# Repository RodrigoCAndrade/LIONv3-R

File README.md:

<div align="center">
  
</div>

<h1 align="center">LIONv3-R Module</h1>

<p align="center">

</p>

<br>

## Overview

The LIONv3-R is an IoT and Direct-to-Satellite (DtS) board built around the ESP32-C6, with 16 MB of external flash and local connectivity over Wi-Fi, Zigbee and Thread. Its radio supports LR-FHSS alongside conventional LoRa, enabling reliable uplinks to satellites or terrestrial gateways from remote sites, at device densities conventional LoRa cannot sustain. By bridging local wireless networks with satellite reach, the LIONv3-R is a complete, scalable hardware platform for telemetry, global asset tracking and remote sensing.

## Repository Organization

* `docs`: Systems engineering, datasheets, requirements (SRD), and interface control (ICD).
* `hardware`: Native KiCad project, schematics, and manufacturing files.
* `mechanics`: 3D models, technical drawings, and physical integration constraints.
* `software`: Embedded firmware and support testing scripts.

## Releases

<table>
  <thead>
    <tr>
      <th>Render</th>
      <th>Hardware Revision</th>
      <th>Status</th>
      <th>Latest Release</th>
      <th>Date</th>
      <th>Datasheet</th>
      <th>BOM</th>
      <th>Manufacturing Info</th>
    </tr>
  </thead>
  <tbody>
    <tr>
      <td></td>
      <td>LIONv3-R</td>
      <td>🚧 Development</td>
      <td><a href="#">-</a></td>
      <td>18-08-2026</td>
      <td><a href="#">PDF</a></td>
      <td>-</td>
      <td><a href="#">Gerber</a></td>
    </tr>
  </tbody>
</table>

## Contributing

We welcome contributions to this project! To ensure a smooth collaboration and maintain our engineering standards, please review our [Contribution Guidelines](CONTRIBUTING.md) before opening any issues, modifying the hardware design, or submitting pull requests.

## References

This board was developed from scratch, but draws on the earlier LIONv1 and LIONv2 designed by [Diego Anestor Coutinho](https://github.com/DIEGOVZK) and [Arielli Ajudarte](https://github.com/ari-aju). The v3 introduces several improvements:

- Dedicated low-power MCU on board
- LR-FHSS support and a more capable LoRa transceiver, covering both sub-GHz and S-band
- External flash for store-and-forward applications
- More efficient antenna
- More compact form factor

## License

This project utilizes a dual-licensing approach to maximize flexibility and adoption:

* **Hardware:** The hardware designs and schematics are licensed under the permissive **[CERN-OHL-P-2.0](hardware/LICENSE)** open-hardware license. You are entirely free to use, modify, distribute, and commercialize the design without any copyleft obligations to share your derived works under the same terms.
* **Software:** All embedded firmware and utility scripts are licensed under the **[MIT License](software/LICENSE)**. You are free to use, modify, and distribute the code without restriction, provided the original copyright notice and permission notice are included.

## Acknowledgments

This work was carried out at the National Institute of Telecommunications (Inatel) with the support of three research laboratories. The EMBRAPII Inatel Competence Center for 5G and 6G Networks [(xGMobile)](https://inatel.br/xgmobile/) supported this project through its Talent Development Program (PFT xGMobile), alongside the Radio & Communication Laboratory [(RadioCom Lab)](https://inatel.br/radiocomlab/) and the Wireless and Artificial Intelligence Laboratory [(WAI Lab)](https://inatel.br/wailab/). Many thanks to the researchers and staff of all three laboratories for their help and for the infrastructure that made the LIONv3-R possible.

<p align="center">
  <sub>Built with ❤️ by <a href="https://rodrigoandrade.com">Rodrigo de Carvalho Andrade</a></sub>
</p>

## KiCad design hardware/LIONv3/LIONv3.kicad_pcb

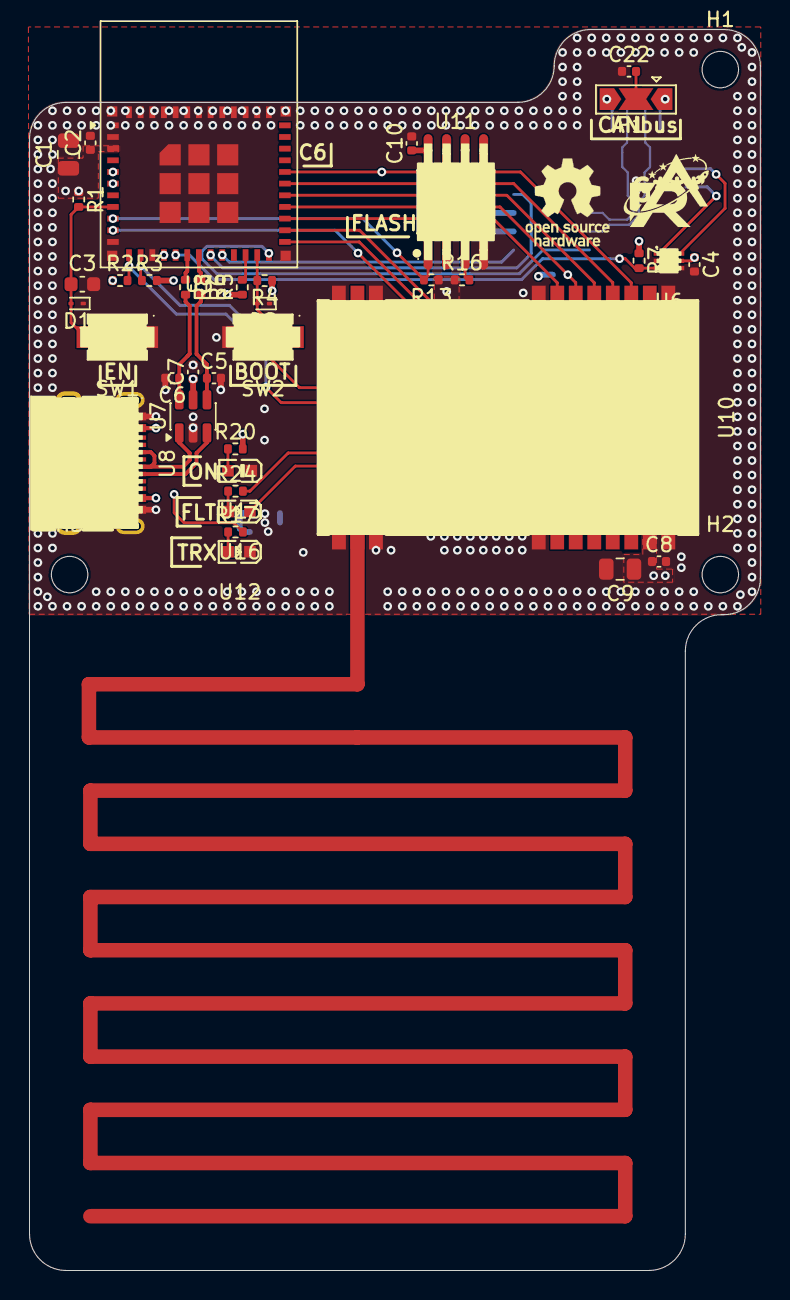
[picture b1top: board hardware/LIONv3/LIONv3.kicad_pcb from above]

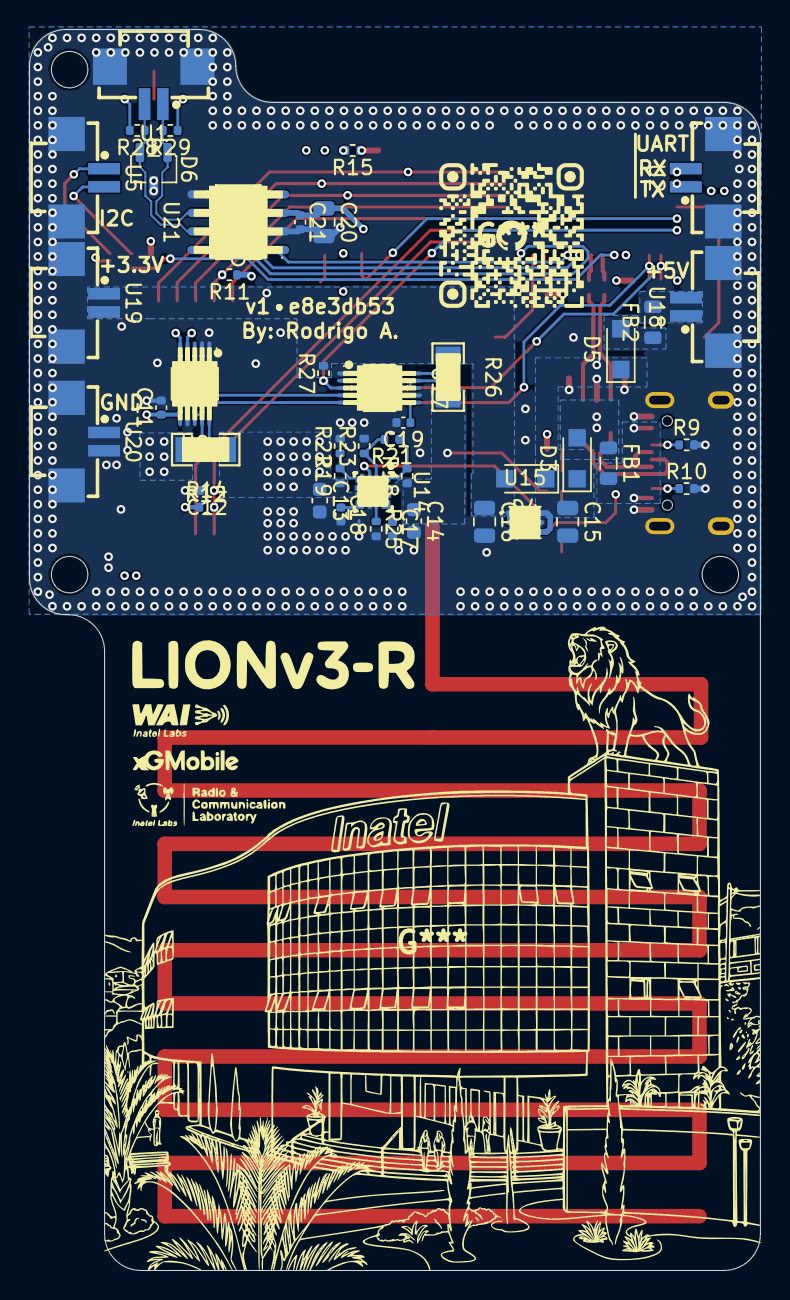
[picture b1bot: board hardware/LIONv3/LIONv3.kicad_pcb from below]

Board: 4 copper layers, 50.1 x 85.2 mm, 85 parts (44 on the bottom side), 56 nets.

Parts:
C1, C9, C15, C16: 22uF; C_0805_2012Metric
C2, C4, C7, C8, C10, C11, C12, C19, C21: 100nF; C_0402_1005Metric
C3, C13, C14: 1uF; C_0603_1608Metric
C5, C6: DNP; C_0402_1005Metric
C17: 3.3nF; C_0402_1005Metric
C18: 2.2nF; C_0402_1005Metric
C20: 10uF; C_0805_2012Metric
C22: 4.7nF; C_0402_1005Metric
D1, D2: ESD9B3.3ST5G; D_SOD-923
D3, D4, D5: PMEG2010ER; Nexperia_CFP3_SOD-123W
D6: TI ESD752DBZR; SOT-23-3
FB1, FB2: BLM21PG221SN1D; L_0805_2012Metric
H1, H2, H3: MountingHole_Pad; MountingHole_2.5mm
JP1: SolderJumper_3_Open; SolderJumper-3_P2.0mm_Open_TrianglePad1.0x1.5mm
R1, R4, R5, R11, R13, R14, R15, R16, R21, R22, R27: 10k; R_0402_1005Metric
R2, R3, R7: 4.7k; R_0402_1005Metric
R6, R8: 0; R_0402_1005Metric
R9, R10: 5.1k; R_0402_1005Metric
R12, R26: 50m; R1206
R17, R20: 120; R_0402_1005Metric
R18: 60.4k; R_0402_1005Metric
R19: 15k; R_0402_1005Metric
R23: 34.8k; R_0402_1005Metric
R24: 430; R_0402_1005Metric
R25: 3.32k; R_0402_1005Metric
R28, R29: 59; R_0402_1005Metric
SW1: RESET; KEY-SMD_L3.9-W3.0-LS5.0
SW2: BOOT; KEY-SMD_L3.9-W3.0-LS5.0
U1, U2, U5, U18, U19, U20: HC-1_25-2PWT; CONN-SMD_2P-P1.25-HC-1.25-2PWT
U3: ESP32-C6-MINI-1-N4; ESP32-C6-MINI-1
U6: TMP112AIDRLR; SOT-563_L1.6-W1.2-P0.50-LS1.6-BR
U7: USBLC6-2SC6; SOT-23-6
U8: TYPE-C_16PIN_2MD(073); USB-C-SMD_TYPE-C-16PIN-2MD-073
U9, U17: INA226AIDGSR; MSOP-10_L3.0-W3.0-P0.50-LS5.0-BL
U10: E80-900M2213S; WIFIM-SMD_22P-L26.0-W16.0-P1.27-TL
U11: W25Q16JVSSIQTR; SOIC-8_L5.3-W5.3-P1.27-LS8.0-BL
U12: XL-1608UBC-04; LED0603-RD_BLUE
U13: XL-1608UGC-04; LED0603-RD_GREEN
U14: TPS259474ARPWR; VQFN-10_L2.0-W2.0-P0.45-TL
U15: TLV76733DRVR; WSON-6_L2.0-W2.0-P0.65-TL-EP
U16: XL-1608SURC-06; LED0603-RD_RED
U21: TCAN3414DR; SOIC-8_L4.9-W3.9-P1.27-LS6.0-BL

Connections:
3.3V_RF: C8.1, C9.1, R12.2, R14.1, U9.8 (VBUS), U9.9 (VIN-), U10.25 (VCC)
+3.3V: C1.1, C2.1, C4.1, C10.1, C11.1, C13.1, C20.1, C21.1, R1.1, R2.1, R3.2, R4.1, R5.1, R7.1, R11.1, R12.1, R13.1, R15.1, R16.1, R19.1, R20.2, U3.3 (3V3), U6.5 (V+), U9.6 (VS+), U9.10 (VIN+), U11.8 (VCC), U14.6 (OUT), U21.3 (VCC)
+3.3V_LDO: C16.1, C19.1, D4.2 (A), R26.1, R27.2, U15.1 (OUT), U15.2 (FB/SNS), U17.6 (VS+), U17.10 (VIN+), U19.1, U19.2
+3.3V_eFuse: C14.1, R18.1, R24.2, R26.2, U14.5 (IN), U17.8 (VBUS), U17.9 (VIN-)
+4.69V: C7.1, C15.1, D3.1 (K), D4.1 (K), D5.1 (K), U7.5 (VBUS), U15.4 (EN), U15.6 (IN)
/CAN_N: D6.1 (K), R29.2, U1.1, U21.6 (CANL)
/CAN_P: D6.2 (K), R28.1, U1.2, U21.7 (CANH)
/CAN_RX: U3.19 (IO14), U21.4 (RXD)
/CAN_STB: U3.24 (IO18), U21.8 (STB)
/CAN_TX: U3.20 (IO15), U21.1 (TXD)
/D+: U7.3 (I/O2), U8.A6 (Dp1), U8.B6 (Dp2)
/D-: U7.1 (I/O1), U8.A7 (Dn1), U8.B7 (Dn2)
/ESP_USB_D+: R6.1, U3.18 (IO13)
/ESP_USB_D-: R8.1, U3.17 (IO12)
/FLASH_CS#: R13.2, U3.9 (IO4), U11.1 (CS#)
/I2C_SCL: R3.1, U3.13 (IO1), U5.2, U6.1 (SCL), U9.5 (SCL), U17.5 (SCL)
/I2C_SDA: R2.2, U3.12 (IO0), U5.1, U6.6 (SDA), U9.4 (SDA), U17.2 (A0), U17.4 (SDA)
/INA_ALERT: R27.1, U3.10 (IO5), U17.3 (Alert)
/IO8: R5.2, U3.22 (IO8)
/IO9: D2.2 (A2), R4.2, SW2.1, U3.23 (IO9)
/LR_BUSY: U3.27 (IO21), U10.7 (BUSY)
/LR_CS#: R11.2, U3.28 (IO22), U10.6 (CS#)
/LR_IRQ: U3.26 (IO20), U10.22 (DIO9)
/LR_LED: R17.2, U3.15 (IO6)
/LR_RST: C12.1, R14.2, U3.25 (IO19), U10.21 (LR_NRESET)
/POWER/LED_FAULT: U14.3 (PG/AUXOFF), U16.1 (K)
/SPI_PICO: U3.30 (RXD0), U10.4 (PICO), U11.5 (DI/IO0)
/SPI_POCI: U3.31 (TXD0), U10.3 (POCI), U11.2 (DO/IO1)
/SPI_SCK: U3.29 (IO23), U10.5 (SCK), U11.6 (CLK)
/TMP_ALERT: R7.2, U3.16 (IO7), U6.3 (ALERT)
/UART_RX: U2.2, U3.5 (IO2)
/UART_TX: U2.1, U3.6 (IO3)
/USB_D+: C5.1, R6.2, U7.4 (I/O2)
/USB_D-: C6.1, R8.2, U7.6 (I/O1)
GND: C1.2, C2.2, C3.2, C4.2, C5.2, C6.2, C7.2, C8.2, C9.2, C10.2, C11.2, C12.2, C13.2, C14.2, C15.2, C16.2, C17.2, C18.2, C19.2, C20.2, C21.2, C22.1, D1.1 (A1), D2.1 (A1), D6.3 (A), R9.2, R10.2, R22.2, R23.2, R25.2, SW1.1, SW2.2, U1.3, U1.4, U2.3, U2.4, U3.1 (GND), U3.2 (GND), U3.11 (GND), U3.14 (GND), U3.36 (GND), U3.37 (GND), U3.38 (GND), U3.39 (GND), U3.40 (GND), U3.41 (GND), U3.42 (GND), U3.43 (GND), U3.44 (GND), U3.45 (GND), U3.46 (GND), U3.47 (GND), U3.48 (GND), U3.49 (GND), U3.50 (GND), U3.51 (GND), U3.52 (GND), U3.53 (GND), U5.3, U5.4, U6.2 (GND), U6.4 (ADD0), U7.2 (GND), U8.13 (EH), U8.14 (EH), U8.A1B12 (GND), U8.B1A12 (GND), U9.1 (A1), U9.2 (A0), U9.7 (GND), U10.1 (GND), U10.8 (GND), U10.11 (GND), U10.13 (GND), U10.14 (GND), U10.16 (GND), U10.19 (GND), U10.26 (GND), U11.4 (GND), U12.1 (K), U13.1 (K), U14.8 (GND), U15.3 (GND), U15.5 (GND), U15.7 (EP), U17.1 (A1), U17.7 (GND), U18.3, U18.4, U19.3, U19.4, U20.1, U20.2, U20.3, U20.4, U21.2 (GND), U21.5 (SHDN/VIO)
unnamed: C3.1, D1.2 (A2), R1.2, SW1.2, U3.8 (EN)
unnamed: D3.2 (A), FB1.1
unnamed: D5.2 (A), FB2.1
unnamed: FB1.2, U8.A4B9 (VBUS), U8.B4A9 (VBUS)
unnamed: FB2.2, U18.1, U18.2
unnamed: JP1.1 (A), R28.2
unnamed: JP1.3 (B), R29.1
unnamed: C22.2, JP1.2 (C)
unnamed: R9.1, U8.A5 (CC1)
unnamed: R10.1, U8.B5 (CC2)
unnamed: R16.2, U11.3 (IO2)
unnamed: R15.2, U11.7 (IO3)
unnamed: R17.1, U12.2 (A)
unnamed: R20.1, U13.2 (A)
unnamed: C18.1, U14.7 (DVDT)
unnamed: R18.2, R21.1, U14.1 (EN/UVLO)
unnamed: R19.2, R22.1, U14.4 (FLT#/PGTH)
unnamed: R25.1, U14.9 (ILM)
unnamed: C17.1, U14.10 (ITIMER)
unnamed: R21.2, R23.1, U14.2 (OVLO/OVCSEL)
unnamed: R24.1, U16.2 (A)

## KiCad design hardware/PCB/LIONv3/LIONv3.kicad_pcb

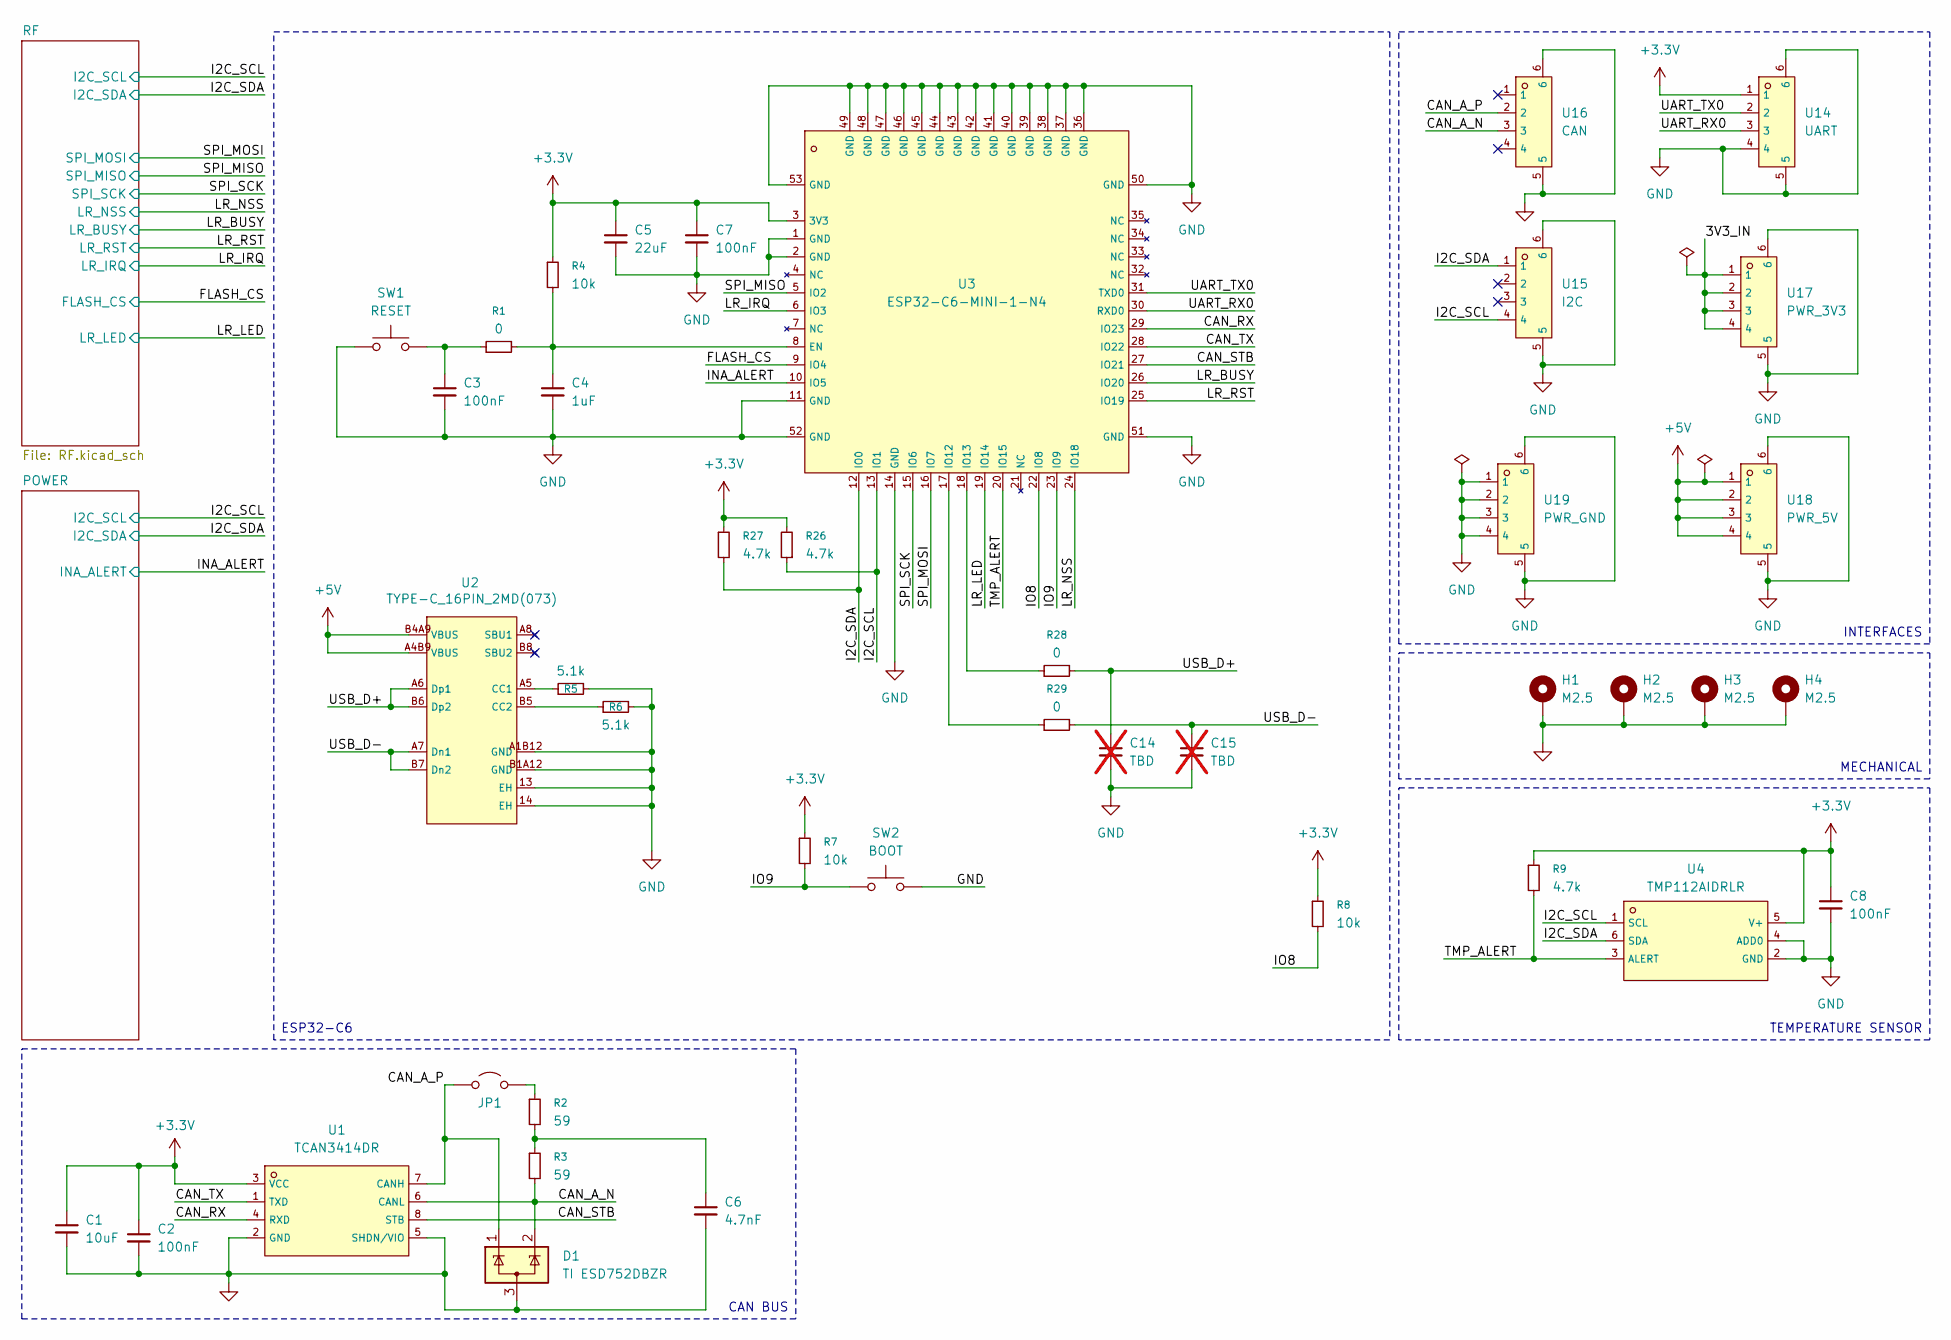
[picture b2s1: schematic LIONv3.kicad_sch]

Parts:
C1: 10uF; C_0805_2012Metric; LCSC C440198
C2, C3, C7, C8: 100nF; C_0402_1005Metric; LCSC C307331
C4: 1uF; C_0603_1608Metric; LCSC C15849
C5: 22uF; C_0805_2012Metric; LCSC C45783
C6: 4.7nF; C_0402_1005Metric; LCSC C1538
C14, C15: TBD; C_0402_1005Metric; not fitted
D1: TI ESD752DBZR; SOT-23-3; LCSC C20345397
H1, H2, H3, H4: M2.5; MountingHole_2.5mm_Pad_Via
JP1: Jumper_2_Open; SolderJumper-2_P1.3mm_Open_TrianglePad1.0x1.5mm
R1, R28, R29: 0; R_0402_1005Metric; LCSC C17168
R2, R3: 59; R_0402_1005Metric; LCSC C2998103
R4, R7, R8: 10k; R_0402_1005Metric; LCSC C25744
R5, R6: 5.1k; R_0402_1005Metric; LCSC C25905
R9, R26, R27: 4.7k; R_0402_1005Metric; LCSC C25900
SW1: RESET; KEY-SMD_L3.9-W3.0-LS5.0; LCSC C5373431
SW2: BOOT; KEY-SMD_L3.9-W3.0-LS5.0; LCSC C5373431
U1: TCAN3414DR; SOIC-8_L4.9-W3.9-P1.27-LS6.0-BL; LCSC C22396693
U2: TYPE-C_16PIN_2MD(073); USB-C-SMD_TYPE-C-16PIN-2MD-073; LCSC C2765186
U3: ESP32-C6-MINI-1-N4; WIFIM-SMD_61P-L16.6-W13.2-P0.80-ESP32-C6-MINI-1-N4; LCSC C5736265
U4: TMP112AIDRLR; SOT-563_L1.6-W1.2-P0.50-LS1.6-BR; LCSC C28927
U14: UART; CONN-SMD_4P-P1.25_53261-0471; LCSC C696092
U15: I2C; CONN-SMD_4P-P1.25_53261-0471; LCSC C696092
U16: CAN; CONN-SMD_4P-P1.25_53261-0471; LCSC C696092
U17: PWR_3V3; CONN-SMD_4P-P1.25_53261-0471; LCSC C696092
U18: PWR_5V; CONN-SMD_4P-P1.25_53261-0471; LCSC C696092
U19: PWR_GND; CONN-SMD_4P-P1.25_53261-0471; LCSC C696092

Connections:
+3.3V: C1.1, C2.1, C5.1, C7.1, C8.1, R4.1, R7.1, R8.1, R9.1, R26.2, R27.1, U1.3 (VCC), U3.3 (3V3), U4.5 (V+), U14.1; also elsewhere on the board
+5V: U2.A4B9 (VBUS), U2.B4A9 (VBUS), U18.1, U18.2, U18.3, U18.4; also elsewhere on the board
/3V3_IN: U17.1, U17.2, U17.3, U17.4
/CAN_A_N: D1.2 (K), R3.2, U1.6 (CANL), U16.3
/CAN_A_P: D1.1 (K), JP1.1 (A), U1.7 (CANH), U16.2
/CAN_RX: U1.4 (RXD), U3.29 (IO23)
/CAN_STB: U1.8 (STB), U3.27 (IO21)
/CAN_TX: U1.1 (TXD), U3.28 (IO22)
/FLASH_CS: U3.9 (IO4); also elsewhere on the board
/I2C_SCL: R26.1, U3.13 (IO1), U4.1 (SCL), U15.4; also elsewhere on the board
/I2C_SDA: R27.2, U3.12 (IO0), U4.6 (SDA), U15.1; also elsewhere on the board
/INA_ALERT: U3.10 (IO5); also elsewhere on the board
/IO8: R8.2, U3.22 (IO8)
/IO9: R7.2, SW2.1, U3.23 (IO9)
/LR_BUSY: U3.26 (IO20); also elsewhere on the board
/LR_IRQ: U3.6 (IO3); also elsewhere on the board
/LR_LED: U3.19 (IO14); also elsewhere on the board
/LR_NSS: U3.24 (IO18); also elsewhere on the board
/LR_RST: U3.25 (IO19); also elsewhere on the board
/SPI_MISO: U3.5 (IO2); also elsewhere on the board
/SPI_MOSI: U3.16 (IO7); also elsewhere on the board
/SPI_SCK: U3.15 (IO6); also elsewhere on the board
/TMP_ALERT: R9.2, U3.20 (IO15), U4.3 (ALERT)
/UART_RX0: U3.30 (RXD0), U14.3
/UART_TX0: U3.31 (TXD0), U14.2
/USB_D+: C14.1, R28.2, U2.A6 (Dp1), U2.B6 (Dp2)
/USB_D-: C15.1, R29.2, U2.A7 (Dn1), U2.B7 (Dn2)
GND: C1.2, C2.2, C3.2, C4.2, C5.2, C6.2, C7.2, C8.2, C14.2, C15.2, D1.3 (A), H1.1, H2.1, H3.1, H4.1, R5.2, R6.2, SW1.1, SW2.2, U1.2 (GND), U1.5 (SHDN/VIO), U2.13 (EH), U2.14 (EH), U2.A1B12 (GND), U2.B1A12 (GND), U3.1 (GND), U3.2 (GND), U3.11 (GND), U3.14 (GND), U3.36 (GND), U3.37 (GND), U3.38 (GND), U3.39 (GND), U3.40 (GND), U3.41 (GND), U3.42 (GND), U3.43 (GND), U3.44 (GND), U3.45 (GND), U3.46 (GND), U3.47 (GND), U3.48 (GND), U3.49 (GND), U3.50 (GND), U3.51 (GND), U3.52 (GND), U3.53 (GND), U4.2 (GND), U4.4 (ADD0), U14.4, U14.5, U14.6, U15.5, U15.6, U16.5, U16.6, U17.5, U17.6, U18.5, U18.6, U19.1, U19.2, U19.3, U19.4, U19.5, U19.6; also elsewhere on the board
unnamed: C3.1, R1.1, SW1.2
unnamed: C6.1, R2.2, R3.1
unnamed: JP1.2 (B), R2.1
unnamed: R5.1, U2.A5 (CC1)
unnamed: R6.1, U2.B5 (CC2)
unnamed: C4.1, R1.2, R4.2, U3.8 (EN)
unnamed: R29.1, U3.17 (IO12)
unnamed: R28.1, U3.18 (IO13)

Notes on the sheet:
MECHANICAL
CAN BUS
TEMPERATURE SENSOR
INTERFACES
ESP32-C6

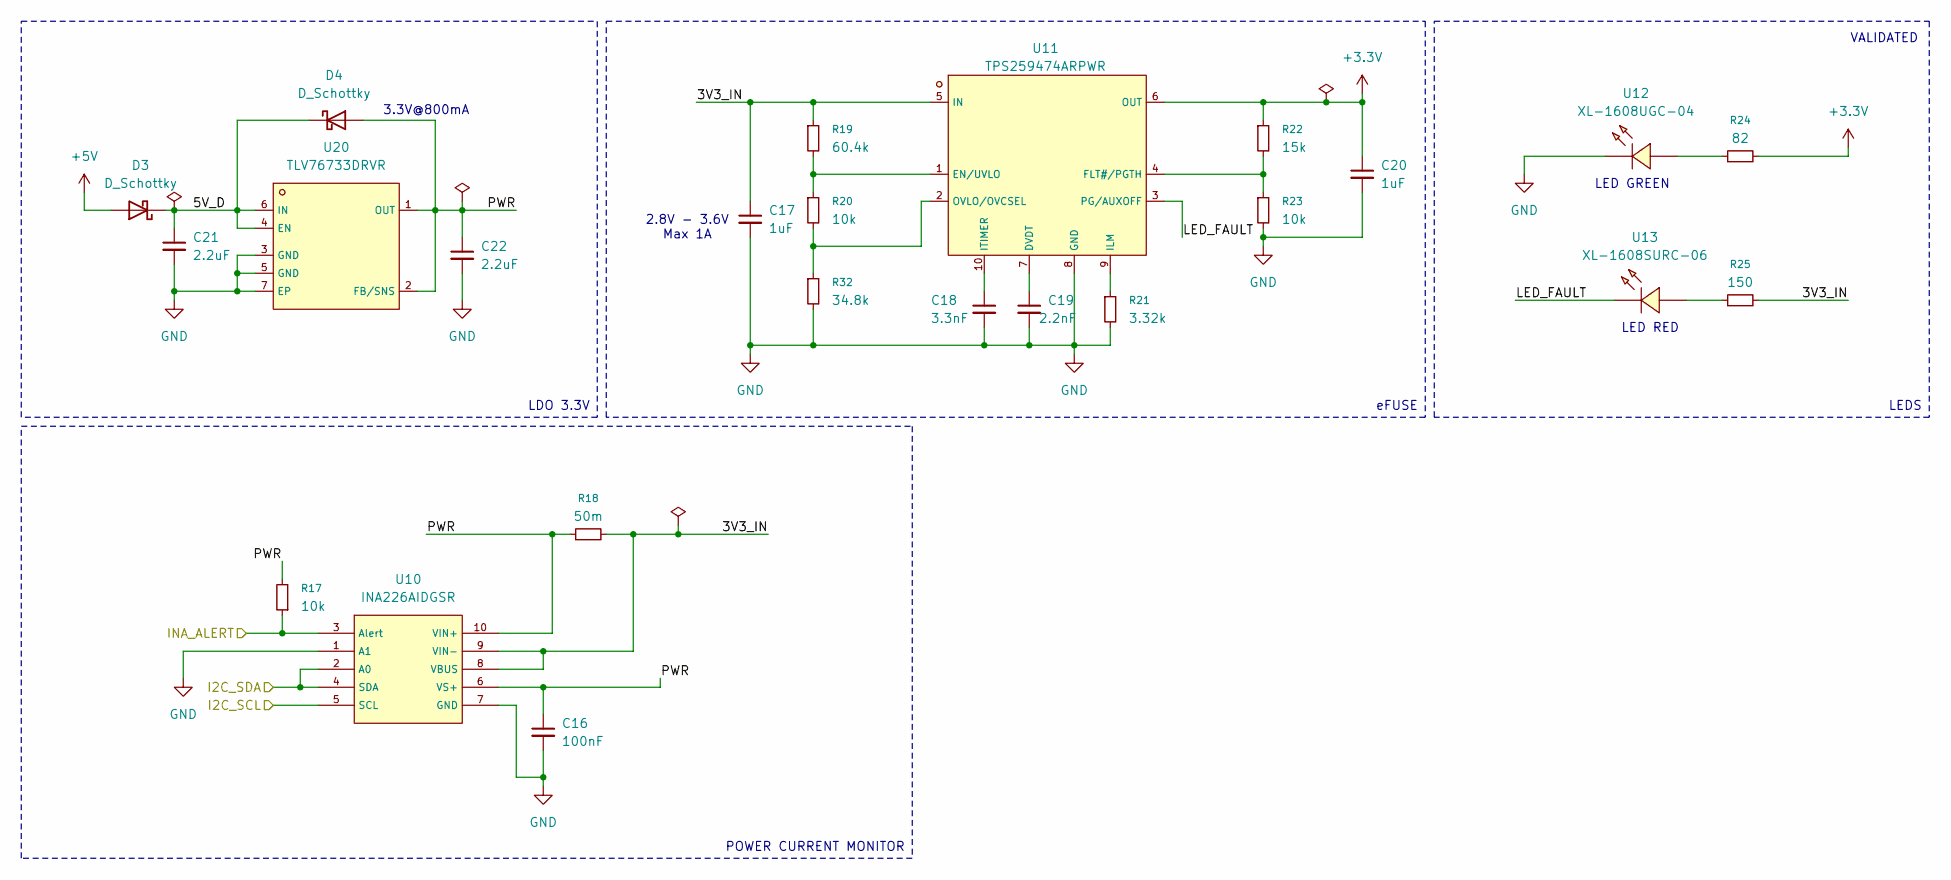
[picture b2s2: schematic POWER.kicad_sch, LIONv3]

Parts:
C16: 100nF; C_0402_1005Metric; LCSC C307331
C17, C20: 1uF; C_0402_1005Metric; LCSC C15849
C18: 3.3nF; C_0402_1005Metric; LCSC C3881585
C19: 2.2nF; C_0402_1005Metric; LCSC C2987940
C21, C22: 2.2uF; C_0603_1608Metric; LCSC C913904
D3, D4: D_Schottky; X2-DFN1006-2_L1.0-W0.6-P0.65-RD; LCSC C2837790
R17, R20, R23: 10k; R_0402_1005Metric; LCSC C25744
R18: 50m; R1206; LCSC C20608719
R19: 60.4k; R_0402_1005Metric; LCSC C2998058
R21: 3.32k; R_0402_1005Metric; LCSC C2998161
R22: 15k; R_0402_1005Metric; LCSC C25756
R24: 82; R_0402_1005Metric; LCSC C2909389
R25: 150; R_0402_1005Metric; LCSC C2909321
R32: 34.8k; R_0402_1005Metric; LCSC C2076772
U10: INA226AIDGSR; MSOP-10_L3.0-W3.0-P0.50-LS5.0-BL; LCSC C49851
U11: TPS259474ARPWR; VQFN-10_L2.0-W2.0-P0.45-TL; LCSC C3662807
U12: XL-1608UGC-04; LED0603-RD_GREEN; LCSC C965804
U13: XL-1608SURC-06; LED0603-RD_RED; LCSC C965799
U20: TLV76733DRVR; WSON-6_L2.0-W2.0-P0.65-TL-EP; LCSC C2848334

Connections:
+3.3V: C20.1, R22.1, R24.2, U11.6 (OUT); also elsewhere on the board
+5V: D3.2 (A); also elsewhere on the board
/I2C_SCL: U10.5 (SCL); also elsewhere on the board
/I2C_SDA: U10.2 (A0), U10.4 (SDA); also elsewhere on the board
/INA_ALERT: R17.1, U10.3 (Alert); also elsewhere on the board
/POWER/3V3_IN: C17.1, R18.2, R19.1, R25.2, U10.8 (VBUS), U10.9 (VIN-), U11.5 (IN)
/POWER/5V_D: C21.1, D3.1 (K), D4.1 (K), U20.4 (EN), U20.6 (IN)
/POWER/LED_FAULT: U11.3 (PG/AUXOFF), U13.1 (K)
/POWER/PWR: C16.1, C22.1, D4.2 (A), R17.2, R18.1, U10.6 (VS+), U10.10 (VIN+), U20.1 (OUT), U20.2 (FB/SNS)
GND: C16.2, C17.2, C18.2, C19.2, C20.2, C21.2, C22.2, R21.2, R23.2, R32.2, U10.1 (A1), U10.7 (GND), U11.8 (GND), U12.1 (K), U20.3 (GND), U20.5 (GND), U20.7 (EP); also elsewhere on the board
unnamed: C19.1, U11.7 (DVDT)
unnamed: R19.2, R20.1, U11.1 (EN/UVLO)
unnamed: R22.2, R23.1, U11.4 (FLT#/PGTH)
unnamed: R21.1, U11.9 (ILM)
unnamed: C18.1, U11.10 (ITIMER)
unnamed: R20.2, R32.1, U11.2 (OVLO/OVCSEL)
unnamed: R24.1, U12.2 (A)
unnamed: R25.1, U13.2 (A)

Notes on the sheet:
3.3V@800mA
2.8V - 3.6V Max 1A
VALIDATED
LED GREEN
LED RED
POWER CURRENT MONITOR
LEDS
LDO 3.3V
eFUSE

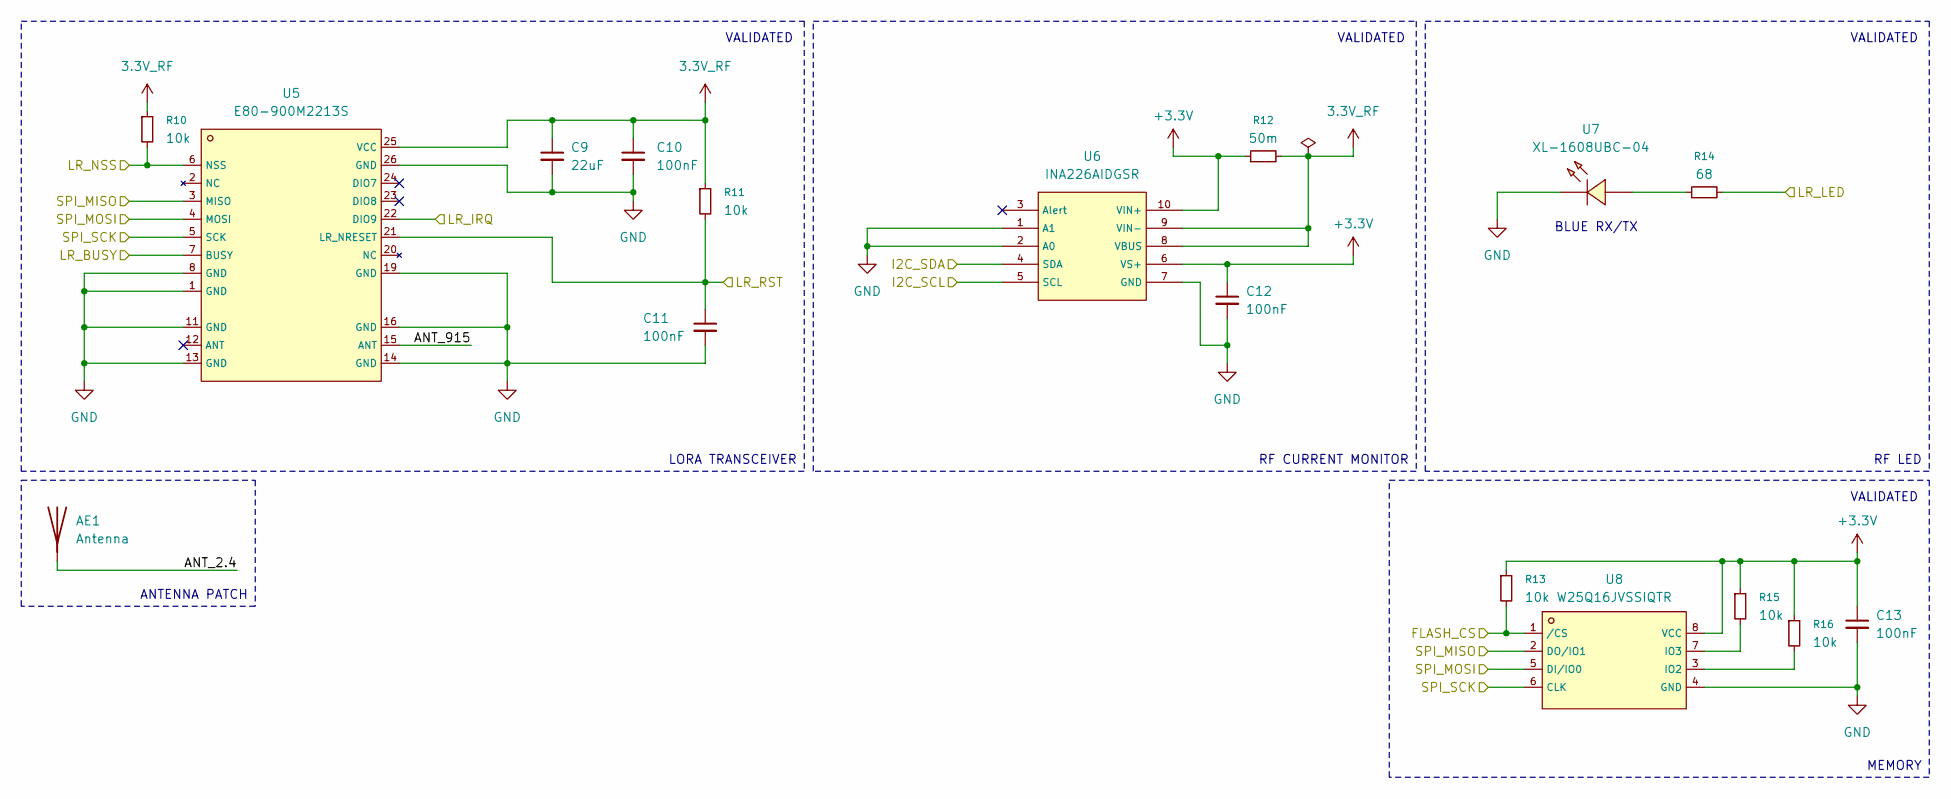
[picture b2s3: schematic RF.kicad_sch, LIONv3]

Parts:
AE1: Antenna
C9: 22uF; C_0805_2012Metric; LCSC C45783
C10, C11, C12, C13: 100nF; C_0402_1005Metric; LCSC C307331
R10, R11, R13, R15, R16: 10k; R_0402_1005Metric; LCSC C25744
R12: 50m; R1206; LCSC C20608719
R14: 68; R_0402_1005Metric; LCSC C2909380
U5: E80-900M2213S; WIFIM-SMD_22P-L26.0-W16.0-P1.27-TL; LCSC C42464134
U6: INA226AIDGSR; MSOP-10_L3.0-W3.0-P0.50-LS5.0-BL; LCSC C49851
U7: XL-1608UBC-04; LED0603-RD_BLUE; LCSC C965807
U8: W25Q16JVSSIQTR; SOIC-8_L5.3-W5.3-P1.27-LS8.0-BL; LCSC C131025

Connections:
3.3V_RF: C9.1, C10.1, R10.1, R11.1, R12.2, U5.25 (VCC), U6.8 (VBUS), U6.9 (VIN-)
+3.3V: C12.1, C13.1, R12.1, R13.1, R15.1, R16.1, U6.6 (VS+), U6.10 (VIN+), U8.8 (VCC); also elsewhere on the board
/FLASH_CS: R13.2, U8.1 (/CS); also elsewhere on the board
/I2C_SCL: U6.5 (SCL); also elsewhere on the board
/I2C_SDA: U6.4 (SDA); also elsewhere on the board
/LR_BUSY: U5.7 (BUSY); also elsewhere on the board
/LR_IRQ: U5.22 (DIO9); also elsewhere on the board
/LR_LED: R14.2; also elsewhere on the board
/LR_NSS: R10.2, U5.6 (NSS); also elsewhere on the board
/LR_RST: C11.1, R11.2, U5.21 (LR_NRESET); also elsewhere on the board
/RF/ANT_915: U5.15 (ANT)
/SPI_MISO: U5.3 (MISO), U8.2 (DO/IO1); also elsewhere on the board
/SPI_MOSI: U5.4 (MOSI), U8.5 (DI/IO0); also elsewhere on the board
/SPI_SCK: U5.5 (SCK), U8.6 (CLK); also elsewhere on the board
GND: C9.2, C10.2, C11.2, C12.2, C13.2, U5.1 (GND), U5.8 (GND), U5.11 (GND), U5.13 (GND), U5.14 (GND), U5.16 (GND), U5.19 (GND), U5.26 (GND), U6.1 (A1), U6.2 (A0), U6.7 (GND), U7.1 (K), U8.4 (GND); also elsewhere on the board
unnamed: R14.1, U7.2 (A)
unnamed: R16.2, U8.3 (IO2)
unnamed: R15.2, U8.7 (IO3)

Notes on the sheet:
BLUE RX/TX
VALIDATED
MEMORY
RF CURRENT MONITOR
LORA TRANSCEIVER
ANTENNA PATCH
RF LED

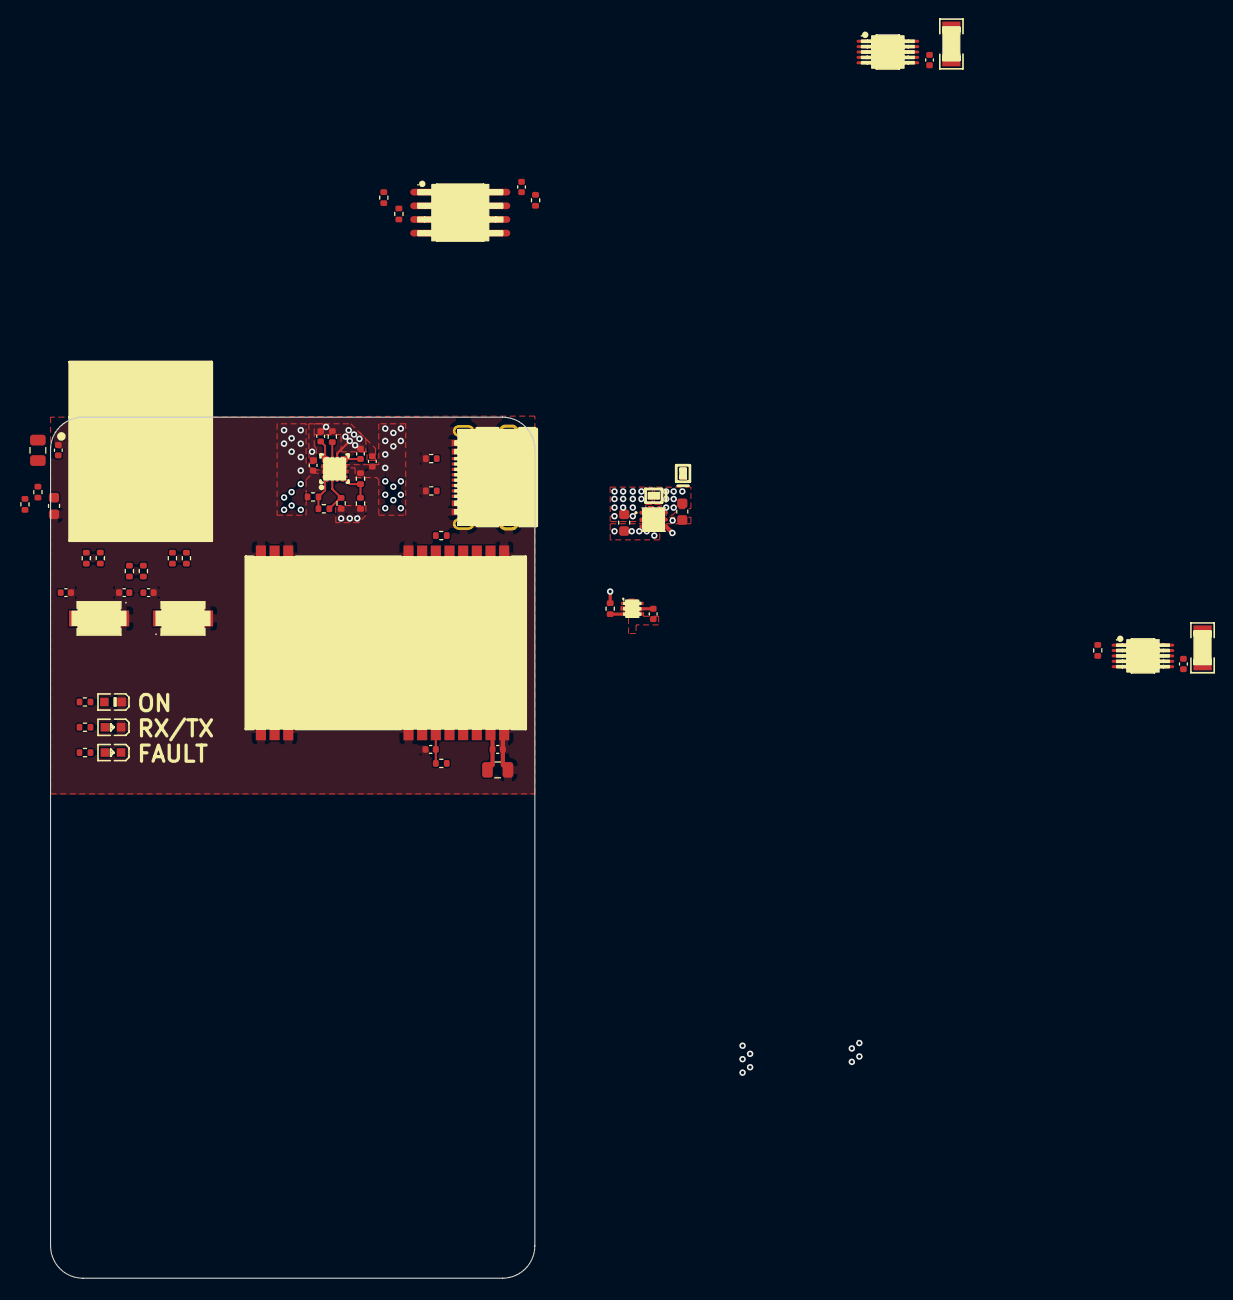
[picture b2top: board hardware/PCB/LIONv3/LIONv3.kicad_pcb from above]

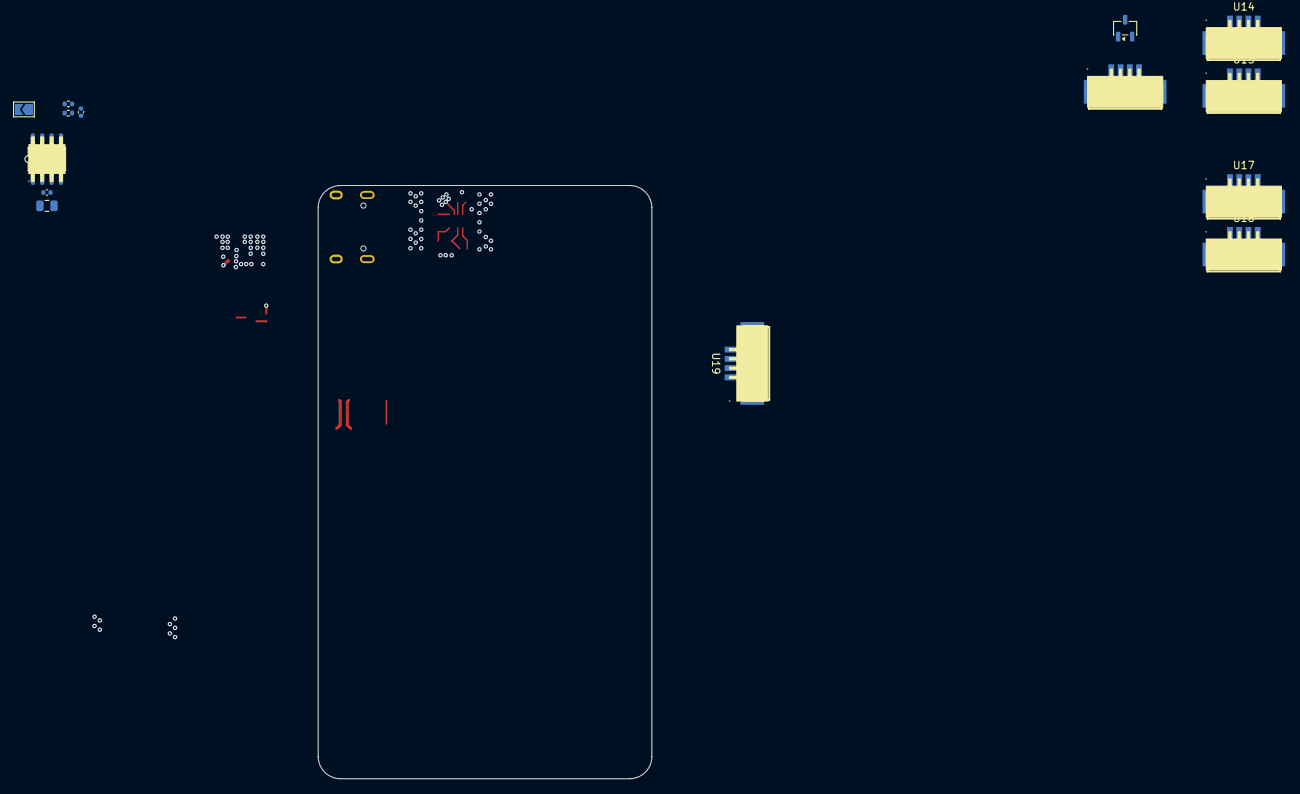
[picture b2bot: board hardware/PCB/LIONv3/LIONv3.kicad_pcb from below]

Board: 4 copper layers, 45.0 x 80.0 mm, 77 parts (14 on the bottom side), 52 nets.
